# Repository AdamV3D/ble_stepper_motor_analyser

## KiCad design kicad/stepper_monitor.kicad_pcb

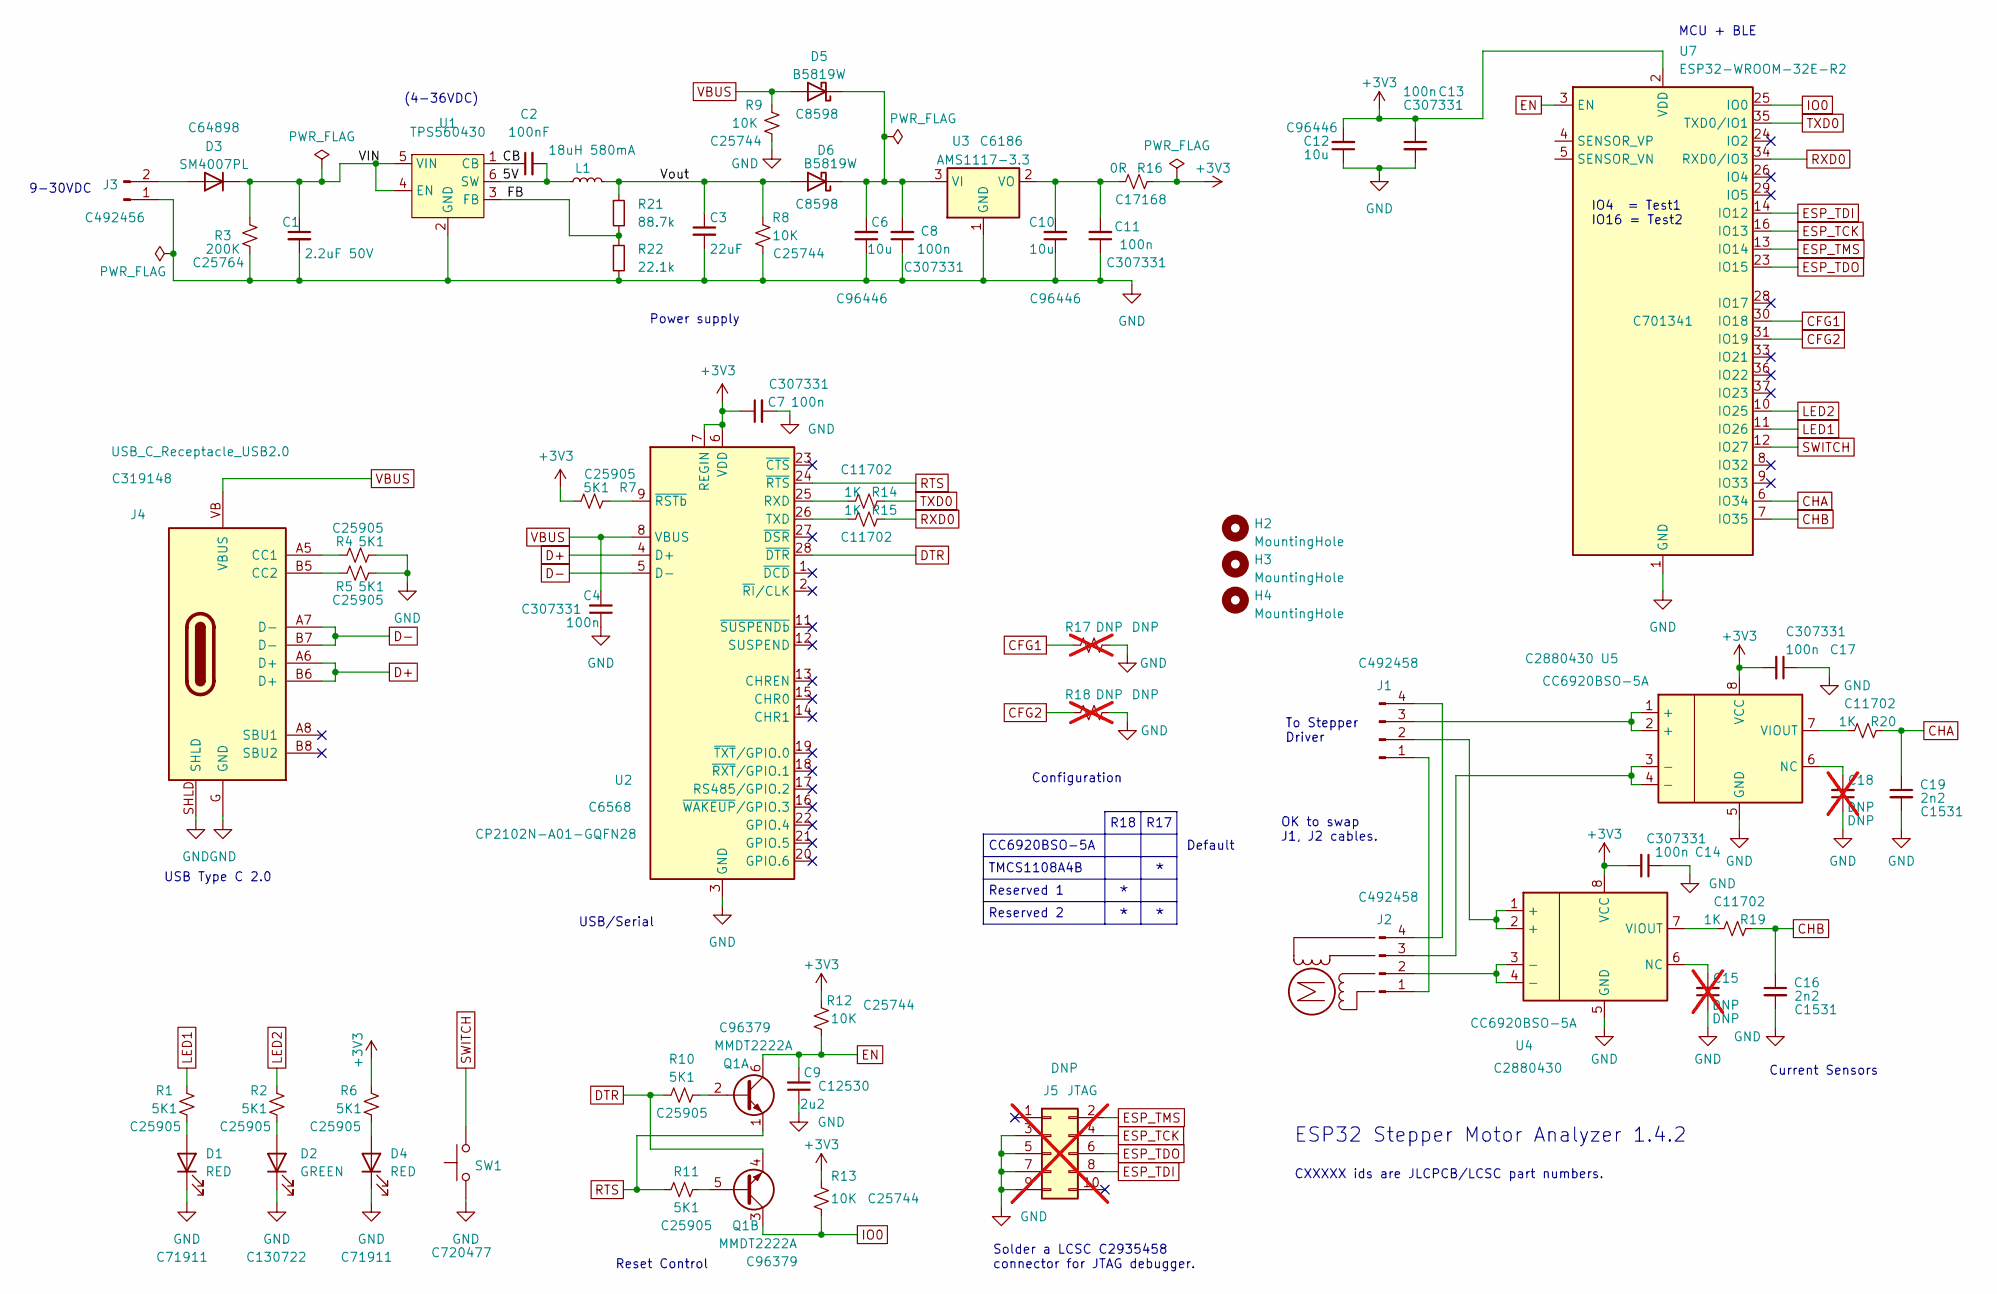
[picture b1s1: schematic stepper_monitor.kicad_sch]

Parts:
C1: 2.2uF 50V; C_0603_1608Metric; LCSC C913904
C2: 100nF; C_0402_1005Metric; LCSC C1525
C3: 22uF; C_0603_1608Metric; LCSC C86295
C4, C7, C8, C11, C13, C14, C17: 100n; C_0402_1005Metric; LCSC C307331
C6, C10, C12: 10u; C_0603_1608Metric; LCSC C96446
C9: 2u2; C_0402_1005Metric; LCSC C12530
C15, C18: DNP; C_0402_1005Metric; LCSC DNP; not fitted
C16, C19: 2n2; C_0402_1005Metric; LCSC C1531
D1, D4: RED; LED_0402_1005Metric_Pad0.77x0.64mm_HandSolder; LCSC C71911
D2: GREEN; LED_0402_1005Metric_Pad0.77x0.64mm_HandSolder; LCSC C130722
D3: SM4007PL; D2_SOD-123; LCSC C64898
D5, D6: B5819W; D_SOD-123; LCSC C8598
H2, H3, H4: MountingHole; MountingHole_3.2mm_M3_Pad_Via
J1, J2: Conn_01x04_Pin; JST_XH_B4B-XH-A_1x04_P2.50mm_Vertical; LCSC C492458
J3: Conn_01x02_Pin; JST_XH_B2B-XH-A_1x02_P2.50mm_Vertical; LCSC C492456
J4: USB_C_Receptacle_USB2.0; USB_C_Receptacle_XKB_U262-16XN-4BVC11; LCSC C319148
J5: JTAG; PinHeader_2x05_P1.27mm_Vertical_SMD; LCSC DNP; not fitted
L1: 18uH 580mA; L_Sunlord_SWPA3012S; LCSC C96833
M1: Motor-simple_stepper_motor_analyzer; Empty
Q1: MMDT2222A; SOT-363_SC-70-6; LCSC C96379
R1, R2, R4, R5, R6, R7, R10, R11: 5K1; R_0402_1005Metric; LCSC C25905
R3: 200K; R_0402_1005Metric; LCSC C25764
R8, R9, R12, R13: 10K; R_0402_1005Metric; LCSC C25744
R14, R15, R19, R20: 1K; R_0402_1005Metric; LCSC C11702
R16: 0R; R_0402_1005Metric; LCSC C17168
R17, R18: DNP; R_0402_1005Metric; LCSC DNP; not fitted
R21: 88.7k; R_0603_1608Metric; LCSC C23258
R22: 22.1k; R_0603_1608Metric; LCSC C25961
SW1: SW_Push; SW_Push_SPST_NO_Alps_SKRK; LCSC C720477
U1: TPS560430; SOT-23-6; LCSC C2863641
U2: CP2102N-A01-GQFN28; QFN-28-1EP_5x5mm_P0.5mm_EP3.35x3.35mm; LCSC C6568
U3: AMS1117-3.3; SOT-223-3_TabPin2; LCSC C6186
U4, U5: CC6920BSO-5A; SOIC-8_3.9x4.9mm_P1.27mm; LCSC C2880430
U7: ESP32-WROOM-32E-R2; ESP32-WROOM-32D; LCSC C701341

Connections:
+3V3: C7.1, C12.2, C13.1, C14.2, C17.2, R6.2, R7.2, R12.2, R13.2, R16.1, U2.6 (VDD), U2.7 (REGIN), U4.8 (VCC), U5.8 (VCC), U7.2 (VDD)
/5V: C2.2, L1.1, U1.6 (SW)
/CB: C2.1, U1.1 (CB)
/FB: R21.2, R22.1, U1.3 (FB)
/VIN: C1.1, D3.1 (K), R3.1, U1.4 (EN), U1.5 (VIN)
/Vout: C3.1, D6.2 (A), L1.2, R8.2, R21.1
CFG1: R17.1, U7.30 (IO18)
CFG2: R18.1, U7.31 (IO19)
CHA: C19.1, R20.1, U7.6 (IO34)
CHB: C16.1, R19.1, U7.7 (IO35)
D+: J4.A6 (D+), J4.B6 (D+), U2.4 (D+)
D-: J4.A7 (D-), J4.B7 (D-), U2.5 (D-)
DTR: Q1.4 (E2), R10.1, U2.28 (~DTR)
EN: C9.2, Q1.6 (C1), R12.1, U7.3 (EN)
ESP_TCK: J5.4, U7.16 (IO13)
ESP_TDI: J5.8, U7.14 (IO12)
ESP_TDO: J5.6, U7.23 (IO15)
ESP_TMS: J5.2, U7.13 (IO14)
GND: C1.2, C3.2, C4.1, C6.1, C7.2, C8.1, C9.1, C10.1, C11.1, C12.1, C13.2, C14.1, C15.1, C16.2, C17.1, C18.1, C19.2, D1.1 (K), D2.1 (K), D4.1 (K), J3.1, J4.G (GND), J4.SHLD, J5.3, J5.5, J5.7, J5.9, R3.2, R4.1, R5.1, R8.1, R9.1, R17.2, R18.2, R22.2, SW1.1, U1.2 (GND), U2.3 (GND), U2.29 (GND), U3.1 (GND), U4.5 (GND), U5.5 (GND), U7.1 (GND), U7.15 (GND), U7.38 (GND), U7.39 (GND)
IO0: Q1.3 (C2), R13.1, U7.25 (IO0)
LED1: R1.2, U7.11 (IO26)
LED2: R2.2, U7.10 (IO25)
unnamed: D1.2 (A), R1.1
unnamed: D2.2 (A), R2.1
unnamed: D3.2 (A), J3.2
unnamed: D4.2 (A), R6.1
unnamed: C6.2, C8.2, D5.1 (K), D6.1 (K), U3.3 (VI)
unnamed: J1.1, J2.1
unnamed: J1.2, U4.1 (+), U4.2 (+)
unnamed: J1.3, U5.1 (+), U5.2 (+)
unnamed: J1.4, J2.4
unnamed: J2.2, U4.3 (-), U4.4 (-)
unnamed: J2.3, U5.3 (-), U5.4 (-)
unnamed: J4.A5 (CC1), R4.2
unnamed: J4.B5 (CC2), R5.2
unnamed: Q1.2 (B1), R10.2
unnamed: Q1.5 (B2), R11.1
unnamed: R14.2, U2.25 (RXD)
unnamed: R15.2, U2.26 (TXD)
unnamed: R7.1, U2.9 (~RSTb)
unnamed: C10.2, C11.2, R16.2, U3.2 (VO)
unnamed: C15.2, U4.6 (NC)
unnamed: R19.2, U4.7 (VIOUT)
unnamed: C18.2, U5.6 (NC)
unnamed: R20.2, U5.7 (VIOUT)
RTS: Q1.1 (E1), R11.2, U2.24 (~RTS)
RXD0: R15.1, U7.34 (RXD0/IO3)
SWITCH: SW1.2, U7.12 (IO27)
TXD0: R14.1, U7.35 (TXD0/IO1)
VBUS: C4.2, D5.2 (A), J4.VB (VBUS), R9.2, U2.8 (VBUS)

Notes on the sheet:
Solder a LCSC C2935458 connector for JTAG debugger.
TMCS1108A4B
Current Sensors
Reserved 2
IO4 = Test1 IO16 = Test2
CXXXXX ids are JLCPCB/LCSC part numbers.
Reserved 1
To Stepper Driver
Configuration
USB Type C 2.0
9-30VDC
USB/Serial
OK to swap J1, J2 cables.
Reset Control
Default
R17
CC6920BSO-5A
R18
MCU + BLE
(4-36VDC)
Power supply
ESP32 Stepper Motor Analyzer 1.4.2

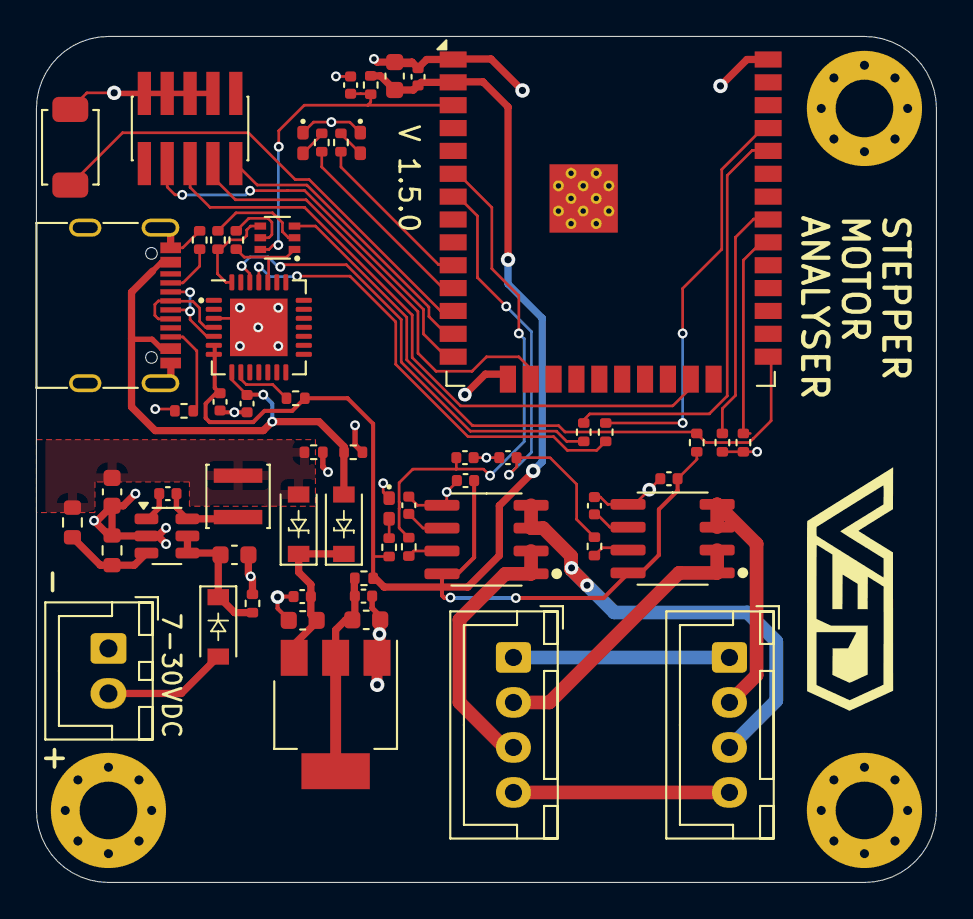
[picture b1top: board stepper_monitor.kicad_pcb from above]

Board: 2 copper layers, 50.0 x 47.0 mm, 63 parts (0 on the bottom side), 50 nets.

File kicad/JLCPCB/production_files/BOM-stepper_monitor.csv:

Comment,Designator,Footprint,LCSC,Quantity
1K,"R14,R15,R19,R20",R_0402_1005Metric,C11702,4
2u2,C9,C_0402_1005Metric,C12530,1
GREEN,D2,LED_0402_1005Metric_Pad0.77x0.64mm_HandSolder,C130722,1
100nF,C2,C_0402_1005Metric,C1525,1
2n2,"C16,C19",C_0402_1005Metric,C1531,2
0R,R16,R_0402_1005Metric,C17168,1
88.7k,R21,R_0603_1608Metric,C23258,1
10K,"R12,R13,R8,R9",R_0402_1005Metric,C25744,4
200K,R3,R_0402_1005Metric,C25764,1
5K1,"R1,R10,R11,R2,R4,R5,R6,R7",R_0402_1005Metric,C25905,8
22.1k,R22,R_0603_1608Metric,C25961,1
TPS560430,U1,SOT-23-6,C2863641,1
CC6920BSO-5A,"U4,U5",SOIC-8_3.9x4.9mm_P1.27mm,C2880430,2
100n,"C11,C13,C14,C17,C4,C7,C8",C_0402_1005Metric,C307331,7
USB_C_Receptacle_USB2.0,J4,USB_C_Receptacle_XKB_U262-16XN-4BVC11,C319148,1
Conn_01x02_Pin,J3,JST_XH_B2B-XH-A_1x02_P2.50mm_Vertical,C492456,1
Conn_01x04_Pin,"J1,J2",JST_XH_B4B-XH-A_1x04_P2.50mm_Vertical,C492458,2
AMS1117-3.3,U3,SOT-223-3_TabPin2,C6186,1
SM4007PL,D3,D2_SOD-123,C64898,1
CP2102N-A01-GQFN28,U2,QFN-28-1EP_5x5mm_P0.5mm_EP3.35x3.35mm,C6568,1
ESP32-WROOM-32E-R2,U7,ESP32-WROOM-32D,C701341,1
RED,"D1,D4",LED_0402_1005Metric_Pad0.77x0.64mm_HandSolder,C71911,2
SW_Push,SW1,SW_Push_SPST_NO_Alps_SKRK,C720477,1
B5819W,"D5,D6",D_SOD-123,C8598,2
22uF,C3,C_0603_1608Metric,C86295,1
2.2uF 50V,C1,C_0603_1608Metric,C913904,1
MMDT2222A,Q1,SOT-363_SC-70-6,C96379,1
10u,"C10,C12,C6",C_0603_1608Metric,C96446,3
18uH 580mA,L1,L_Sunlord_SWPA3012S,C96833,1

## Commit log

2025-01-25 New version without Mornsun regulator
2025-02-03 Fixed R2 and regen BOM
